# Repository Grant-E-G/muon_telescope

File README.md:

# Muon Telescope

This repository contains the complete design record for a two-layer cosmic-ray
muon telescope: electronics, FPGA firmware, host software, mechanical CAD,
manufacturing releases, and measurement records.

The first build is an engineering prototype. It uses two identical
50 x 50 x 10 mm BC-408 plastic-scintillator blocks and a central power/interface
board connected to a Digilent Cora Z7. The instrument is
intended to count single-channel events and two-layer coincidences. It is
**not** an energy spectrometer, position tracker, or scattering-tomography
system.

No PCB is approved for ordering yet. The current design and its remaining
release gates are recorded in [docs/design.md](docs/design.md) and
[docs/build-and-debug.md](docs/build-and-debug.md).

## Read first

1. [docs/design.md](docs/design.md) — authoritative electrical, FPGA, and
   measurement specification.
2. [docs/build-and-debug.md](docs/build-and-debug.md) — staged build, release
   gates, acceptance tests, and pre-populated debugging checklist.
3. [docs/bom.md](docs/bom.md) — sourced planning BOM and cost assumptions.
4. [docs/theory.md](docs/theory.md) — concise explanation of the signal chain
   and what the measurements can support.
5. [CONTRIBUTING.md](CONTRIBUTING.md) — KiCad and Git collaboration rules.

When documents disagree, `docs/design.md` wins unless a reviewed change updates
it. KiCad source becomes authoritative for connectivity only after the schematic
has been reviewed against that specification.

## Repository layout

```text
docs/                       Design, theory, BOM, build, debug, and datasheets
hardware/detector_head/     One KiCad design, assembled twice
hardware/power_interface/   Central power and Cora Z7 interface KiCad design
hardware/libraries/         Project symbols, footprints, and electrical 3D models
hardware/mechanical/        Frame, enclosure, and non-electrical CAD
hardware/manufacturing/     Reviewed, tagged fabrication packages only
firmware/                   Cora Z7 programmable-logic design and constraints
software/                   Host-side capture and analysis tools
data/                       Small, curated calibration and measurement records
scripts/                    Repeatable project checks
```

Keep source files near the subsystem they describe. Do not create another
directory or README unless it removes a real ambiguity. Large raw captures and
third-party source archives do not belong in Git; part datasheets are the
intentional exception and live in `docs/datasheets/`. For large raw captures,
record their external source and a checksum instead.

## Toolchain and routine checks

- KiCad **9.0.9** is the locked hardware file-format version.
- Run `make check` before a hardware pull request and before a fabrication
  release. The reusable checker reads each board's co-located `validation.json`
  and writes consolidated reports plus top/bottom review images under
  `build/checks/`. The run includes design-intent/layout checks and focused
  ngspice models; a clean DRC alone is not treated as validation.
- Preserve project-owned libraries and 3D models in this repository. Use
  project-relative `${KIPRJMOD}` library paths.

## Coding guidelines

- Prefer Rust for implementation work. Use Python as a backup, with type checking.
- Prefer functional code when possible. Relax this guideline when it causes performance issues.
- Long functions are fine.
- Avoid inheritance. Object-oriented design is generally discouraged.
- Avoid excessive code fragmentation. Longer files are acceptable when they keep related logic together.
- Lint code aggressively. Use Black for Python formatting.
- Shorter code is almost always better code.

## Attribution and license

The detector dimensions and front-end starting point were informed by the
[CosmicWatch Desktop Muon Detector v3X](https://github.com/spenceraxani/CosmicWatch-Desktop-Muon-Detector-v3X)
and its [2025 design paper](https://arxiv.org/html/2508.12111). No CosmicWatch
design files are copied here; consult its CC BY-NC 4.0 license before reusing
them. Original material in this repository is licensed under [MIT](LICENSE).

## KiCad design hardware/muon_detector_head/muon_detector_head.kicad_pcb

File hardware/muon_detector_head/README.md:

# Accepted prototype layout judgments: detector head and power/interface boards

The physical prototype release is **v0**, dated **2026-09-18**. Both sides of
both boards carry that identifier; the electrical design intent remains
revision A.

Both boards pass `make check` with no blocking findings. The layout still
contains three documented judgment calls. On 2026-09-17, the project owner
accepted all three as good enough for the revision-A engineering prototypes.
The acceptance freezes these layouts; it does not waive the remaining
physical-part, output-inspection, BOM, or release-package gates in
`docs/build-and-debug.md`.

Run `make check` (it needs KiCad 9.0.9 and `ngspice`) and review the reports
and renders under `build/checks/` alongside this list.

## 1. Relaxed ground-return distance for four bypass capacitors

**Where:** `proximity_checks` in `hardware/muon_detector_head/validation.json`
and `hardware/power_interface/validation.json`.

**What changed:** The checks required a bypass capacitor's ground pad to be
within 3.0 mm of the IC ground pin. On these packages, ground (pin 4) and
supply (pin 8) sit on opposite corners. A single component-side capacitor
therefore cannot be within 3.0 mm of both pins. The supply-side 3.0 mm limit
is unchanged; only the ground-side limit was raised.

| Board | Check | Old limit | New limit | Measured |
|---|---|---:|---:|---:|
| Head | U1 (TPH2502, SOIC-8) to C2 | 3.0 mm | 6.0 mm | 5.91 mm |
| Head | U3 (TPH2502, SOIC-8) to C17 | 3.0 mm | 6.0 mm | 5.91 mm |
| Head | U5 (SN74LVC1G123, DCT-8) to C15 | 3.0 mm | 4.5 mm | 3.92 mm |
| Power | U3 (MCP3202, SOIC-8) to C12 | 3.0 mm | 6.0 mm | 5.99 mm |

A brute-force search over capacitor position and rotation gives about 5.5 mm
as the best possible SOIC-8 result. On the real boards, neighbouring parts
push it to about 5.9 mm.

**Alternatives:** Put the capacitor on the back side (not allowed on the head:
the SiPM must be the only optical-side part). Or change the check to measure
each pad's distance to its own ground via instead of pad-to-pad.

**Resolution:** Accepted for the revision-A engineering prototypes. Retain the
configured limits and the measured-distance checks.

## 2. AMP_OUT passes between the R13 pads at 0.25 mm clearance

**Where:** rule `AMP_OUT between R_CHG pads` in
`hardware/muon_detector_head/muon_detector_head.kicad_dru`.

**Why:** The peak-hold checks place R13 within 3 mm of U3 pin 1, the BAS70
(D2) within 3 mm of C16, and C16 within 3 mm of U3 pin 5. C17 must sit at the
top end of U3. Together these leave the chain U3 pin 1 → R13 → D2 → C16 →
U3 pin 5 wrapped around the left side of U3, fencing in pin 3 (AMP_OUT). The
0.3 mm AMP_OUT trace enters pin 3 through the 0.8 mm gap between R13's pads.
That gives 0.25 mm clearance instead of the normal 0.4 mm. The U3A output, R13
and the diode anode follow AMP_OUT to within a diode drop, so the adjacent
signals are nearly identical. 0.25 mm is well within PCBWay's standard
capability.

**Alternatives:**
- A via pair on AMP_OUT. There is currently no room for the inner via.
- Route the chain around U3's other side. That needs the U3/C17 ground limit
  relaxed to about 7.5 mm.

**Resolution:** Accepted for the revision-A engineering prototypes. Retain the
0.25 mm local clearance rule and current route.

## 3. The PEAK_HOLD guard trace is now only a short piece

**Where:** head PCB around U3, C16, D2, Q1, U4 and TP11.

**Design intent:** `docs/design.md` asks for a narrow `PEAK_GUARD` trace that
surrounds the `PEAK_HOLD` island.

**What exists:** The hold node is now very compact. It runs under the U3 body
to C16, D2 pin 3, the Q1 drain, the U4 D pin (TMUX1101 alternate, DNP) and
TP11. Their neighbouring pads leave no legal room for a guard ring. There is
only:

- the U3 pin 6/7 link to R14, and
- a 3.5 mm guard piece beside Q1.

That piece's open end is the intentional `track_dangling` DRC warning.

**Trade-off:** The hold node is smaller, but less of it is guarded against
surface leakage.

**Alternatives:**
- Move the unfitted U4/C18 alternate out of the island to free space.
- Relax the peak-hold placement checks to make room for a full ring.

**Resolution:** Accepted for the revision-A engineering prototypes. Retain the
compact hold node and short guard piece, and qualify droop and leakage on the
bench as required by `docs/build-and-debug.md`.

## Other items for human review

These `make check` warnings were also accepted for the revision-A engineering
prototypes; they remain visible so bring-up and any future revision can address
measured problems rather than assuming the warnings are harmless:

- **Ground-plane coverage:** some routed nets have less than 95% ground plane
  underneath (listed per net in each report).
- **Bottom-layer routing:** some traces run on the B.Cu ground layer, cutting
  the plane.
- **Power board `TRIG_B`:** the trace is 6% over the one-sixth-edge
  transmission-line screen.
- **Head analytic noise floor:** the estimate is model-limited.

The layout for these changes was generated and edited with scripts, not in
the KiCad GUI. Open both boards in KiCad for the visual review that
`CONTRIBUTING.md` requires. The Gerbers under each `fab/` folder were
regenerated from the current boards. They are not a reviewed manufacturing
release.

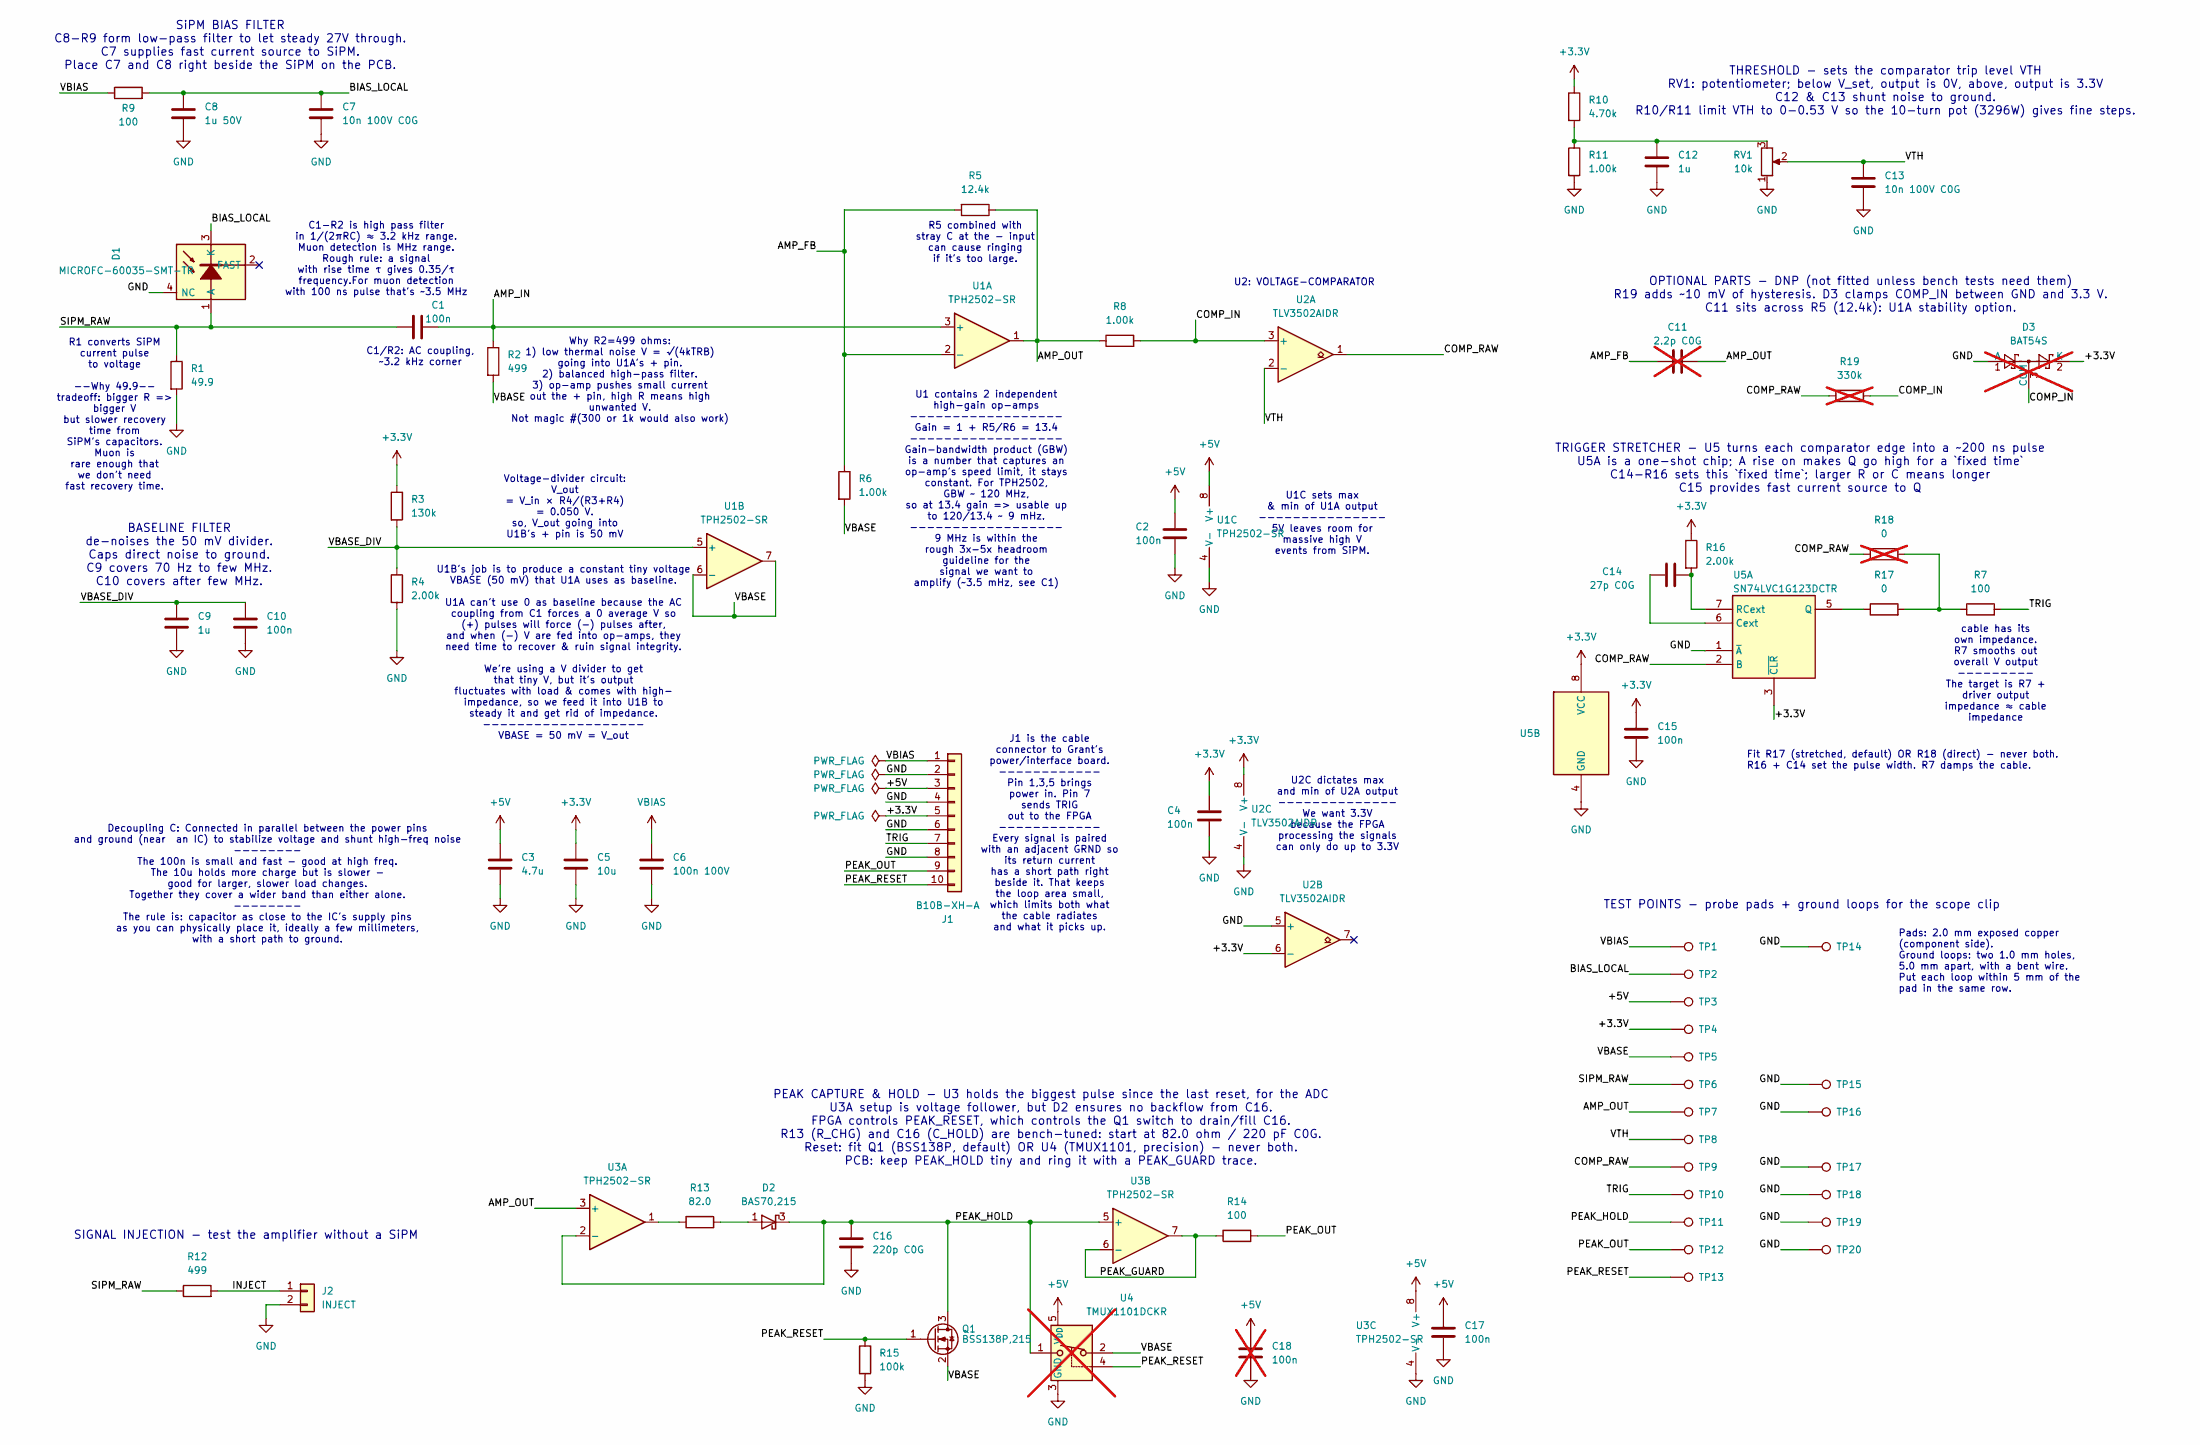
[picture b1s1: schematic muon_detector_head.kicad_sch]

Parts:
C1, C2, C4, C10, C15, C17: 100n; C_0805_2012Metric
C3: 4.7u; C_0805_2012Metric
C5: 10u; C_0805_2012Metric
C6: 100n 100V; C_0805_2012Metric
C7, C13: 10n 100V C0G; C_0805_2012Metric
C8: 1u 50V; C_1206_3216Metric
C9, C12: 1u; C_0805_2012Metric
C11: 2.2p C0G; C_0805_2012Metric; not fitted
C14: 27p C0G; C_0805_2012Metric
C16: 220p C0G; C_0805_2012Metric
C18: 100n; C_0805_2012Metric; not fitted
D1: MICROFC-60035-SMT-TR; MICROFC-60035-SMT
D2: BAS70,215; SOT-23
D3: BAT54S; SOT-23; not fitted
J1: B10B-XH-A; JST_XH_B10B-XH-A_1x10_P2.50mm_Vertical
J2: INJECT; PinHeader_1x02_P2.54mm_Vertical
Q1: BSS138P,215; SOT-23
R1: 49.9; R_0805_2012Metric
R2, R12: 499; R_0805_2012Metric
R3: 130k; R_0805_2012Metric
R4, R16: 2.00k; R_0805_2012Metric
R5: 12.4k; R_0805_2012Metric
R6, R8, R11: 1.00k; R_0805_2012Metric
R7, R9, R14: 100; R_0805_2012Metric
R10: 4.70k; R_0805_2012Metric
R13: 82.0; R_0805_2012Metric
R15: 100k; R_0805_2012Metric
R17: 0; R_0805_2012Metric
R18: 0; R_0805_2012Metric; not fitted
R19: 330k; R_0805_2012Metric; not fitted
RV1: 10k; Potentiometer_Bourns_3296W_Vertical
TP1: VBIAS; TestPoint_Pad_D2.0mm
TP2: BIAS_LOCAL; TestPoint_Pad_D2.0mm
TP3: +5V; TestPoint_Pad_D2.0mm
TP4: +3.3V; TestPoint_Pad_D2.0mm
TP5: VBASE; TestPoint_Pad_D2.0mm
TP6: SIPM_RAW; TestPoint_Pad_D2.0mm
TP7: AMP_OUT; TestPoint_Pad_D2.0mm
TP8: VTH; TestPoint_Pad_D2.0mm
TP9: COMP_RAW; TestPoint_Pad_D2.0mm
TP10: TRIG; TestPoint_Pad_D2.0mm
TP11: PEAK_HOLD; TestPoint_Pad_D2.0mm
TP12: PEAK_OUT; TestPoint_Pad_D2.0mm
TP13: PEAK_RESET; TestPoint_Pad_D2.0mm
TP14, TP15, TP16, TP17, TP18, TP19, TP20: GND_LOOP; TestPoint_GroundLoop_P5.00mm_Drill1.0mm
U1, U3: TPH2502-SR; SOIC-8_3.9x4.9mm_P1.27mm
U2: TLV3502AIDR; SOIC-8_3.9x4.9mm_P1.27mm
U4: TMUX1101DCKR; SOT-353_SC-70-5; not fitted
U5: SN74LVC1G123DCTR; SSOP-8_2.95x2.8mm_P0.65mm

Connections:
+3.3V: C4.1, C5.1, C15.1, D3.2 (K), J1.5 (+3V3_LOCAL), R3.1, R10.1, R16.1, TP4.1, U2.6 (-), U2.8 (V+), U5.3 (~CLR), U5.8 (VCC)
+5V: C2.1, C3.1, C17.1, C18.1, J1.3 (+5VA), TP3.1, U1.8 (V+), U3.8 (V+), U4.5 (V_{DD})
/AMP_FB: C11.1, R5.2, R6.1, U1.2 (-)
/AMP_IN: C1.2, R2.1, U1.3 (+)
/AMP_OUT: C11.2, R5.1, R8.1, TP7.1, U1.1, U3.3 (+)
/BIAS_LOCAL: C7.1, C8.1, D1.3 (K), R9.2, TP2.1
/COMP_IN: D3.3 (COM), R8.2, R19.2, U2.3 (+)
/COMP_RAW: R18.1, R19.1, TP9.1, U2.1, U5.2 (B)
/INJECT: J2.1, R12.2
/PEAK_GUARD: R14.1, U3.6 (-), U3.7
/PEAK_HOLD: C16.1, D2.3 (K), Q1.3 (D), TP11.1, U3.2 (-), U3.5 (+), U4.1
/PEAK_OUT: J1.9 (PEAK_OUT), R14.2, TP12.1
/PEAK_RESET: J1.10 (PEAK_RESET), Q1.1 (G), R15.1, TP13.1, U4.4
/SIPM_RAW: C1.1, D1.1 (A), R1.1, R12.1, TP6.1
/TRIG: J1.7 (TRIG_OUT), R7.2, TP10.1
/VBASE: Q1.2 (S), R2.2, R6.2, TP5.1, U1.6 (-), U1.7, U4.2
/VBASE_DIV: C9.1, C10.1, R3.2, R4.1, U1.5 (+)
/VTH: C13.1, RV1.2, TP8.1, U2.2 (-)
GND: C2.2, C3.2, C4.2, C5.2, C6.2, C7.2, C8.2, C9.2, C10.2, C12.2, C13.2, C15.2, C16.2, C17.2, C18.2, D1.4 (NC), D3.1 (A), J1.2 (GND), J1.4 (GND), J1.6 (GND), J1.8 (GND), J2.2, R1.2, R4.2, R11.2, R15.2, RV1.1, TP14.1, TP15.1, TP16.1, TP17.1, TP18.1, TP19.1, TP20.1, U1.4 (V-), U2.4 (V-), U2.5 (+), U3.4 (V-), U4.3 (GND), U5.1 (~A), U5.4 (GND)
unnamed: C12.1, R10.2, R11.1, RV1.3
unnamed: D2.1 (A), R13.2
unnamed: R13.1, U3.1
unnamed: R7.1, R17.2, R18.2
unnamed: C14.1, U5.6 (Cext)
unnamed: R17.1, U5.5 (Q)
unnamed: C14.2, R16.2, U5.7 (RCext)
VBIAS: C6.1, J1.1 (BIAS_27V), R9.1, TP1.1

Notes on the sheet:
R1 converts SiPM current pulse to voltage --Why 49.9-- tradeoff: bigger R => bigger V but slower recovery time from SiPM's capacitors. Muon is rare enough that we don't need fast recovery time.
BASELINE FILTER de-noises the 50 mV divider. Caps direct noise to ground. C9 covers 70 Hz to few MHz. C10 covers after few MHz.
SIGNAL INJECTION - test the amplifier without a SiPM
J1 is the cable connector to Grant's power/interface board. ------------ Pin 1,3,5 brings power in. Pin 7 sends TRIG out to the FPGA ------------ Every signal is paired with an adjacent GRND so its return current has a short path right beside it. That keeps the loop area small, which limits both wh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
cable has its own impedance. R7 smooths out overall V output --------- The target is R7 + driver output impedance ≈ cable impedance
Voltage-divider circuit: V_out = V_in × R4/(R3+R4) = 0.050 V. so, V_out going into U1B's + pin is 50 mV
SiPM BIAS FILTER C8-R9 form low-pass filter to let steady 27V through. C7 supplies fast current source to SiPM. Place C7 and C8 right beside the SiPM on the PCB.
OPTIONAL PARTS - DNP (not fitted unless bench tests need them) R19 adds ~10 mV of hysteresis. D3 clamps COMP_IN between GND and 3.3 V. C11 sits across R5 (12.4k): U1A stability option.
U2: VOLTAGE-COMPARATOR
R5 combined with stray C at the − input can cause ringing if it's too large.
Why R2=499 ohms: 1) low thermal noise V = √(4kTRB) going into U1A's + pin. 2) balanced high-pass filter. 3) op-amp pushes small current out the + pin, high R means high unwanted V. Not magic #(300 or 1k would also work)
U1C sets max & min of U1A output --------------- 5V leaves room for massive high V events from SiPM.
U1B's job is to produce a constant tiny voltage VBASE (50 mV) that U1A uses as baseline. U1A can't use 0 as baseline because the AC coupling from C1 forces a 0 average V so (+) pulses will force (-) pulses after, and when (-) V are fed into op-amps, they need time to recover & ruin signal integrity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
TRIGGER STRETCHER - U5 turns each comparator edge into a ~200 ns pulse U5A is a one-shot chip; A rise on makes Q go high for a `fixed time` C14-R16 sets this `fixed time`; larger R or C means longer C15 provides fast current source to Q
TEST POINTS - probe pads + ground loops for the scope clip
Fit R17 (stretched, default) OR R18 (direct) - never both. R16 + C14 set the pulse width. R7 damps the cable.
PEAK CAPTURE & HOLD - U3 holds the biggest pulse since the last reset, for the ADC U3A setup is voltage follower, but D2 ensures no backflow from C16. FPGA controls PEAK_RESET, which controls the Q1 switch to drain/fill C16. R13 (R_CHG) and C16 (C_HOLD) are bench-tuned: start at 82.0 ohm / 220 pF C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
Pads: 2.0 mm exposed copper (component side). Ground loops: two 1.0 mm holes, 5.0 mm apart, with a bent wire. Put each loop within 5 mm of the pad in the same row.
Decoupling C: Connected in parallel between the power pins and ground (near an IC) to stabilize voltage and shunt high-freq noise -------- The 100n is small and fast - good at high freq. The 10u holds more charge but is slower - good for larger, slower load changes. Together they cover a wider band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
C1-R2 is high pass filter in 1/(2πRC) ≈ 3.2 kHz range. Muon detection is MHz range. Rough rule: a signal with rise time τ gives 0.35/τ frequency.For muon detection with 100 ns pulse that's ~3.5 MHz
U1 contains 2 independent high-gain op-amps ------------------ Gain = 1 + R5/R6 = 13.4 ------------------ Gain-bandwidth product (GBW) is a number that captures an op-amp's speed limit, it stays constant. For TPH2502, GBW ~ 120 MHz, so at 13.4 gain => usable up to 120/13.4 ~ 9 mHz. ----------------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
C1/R2: AC coupling, ~3.2 kHz corner
U2C dictates max and min of U2A output -------------- We want 3.3V because the FPGA processing the signals can only do up to 3.3V
THRESHOLD - sets the comparator trip level VTH RV1: potentiometer; below V_set, output is 0V, above, output is 3.3V C12 & C13 shunt noise to ground. R10/R11 limit VTH to 0-0.53 V so the 10-turn pot (3296W) gives fine steps.

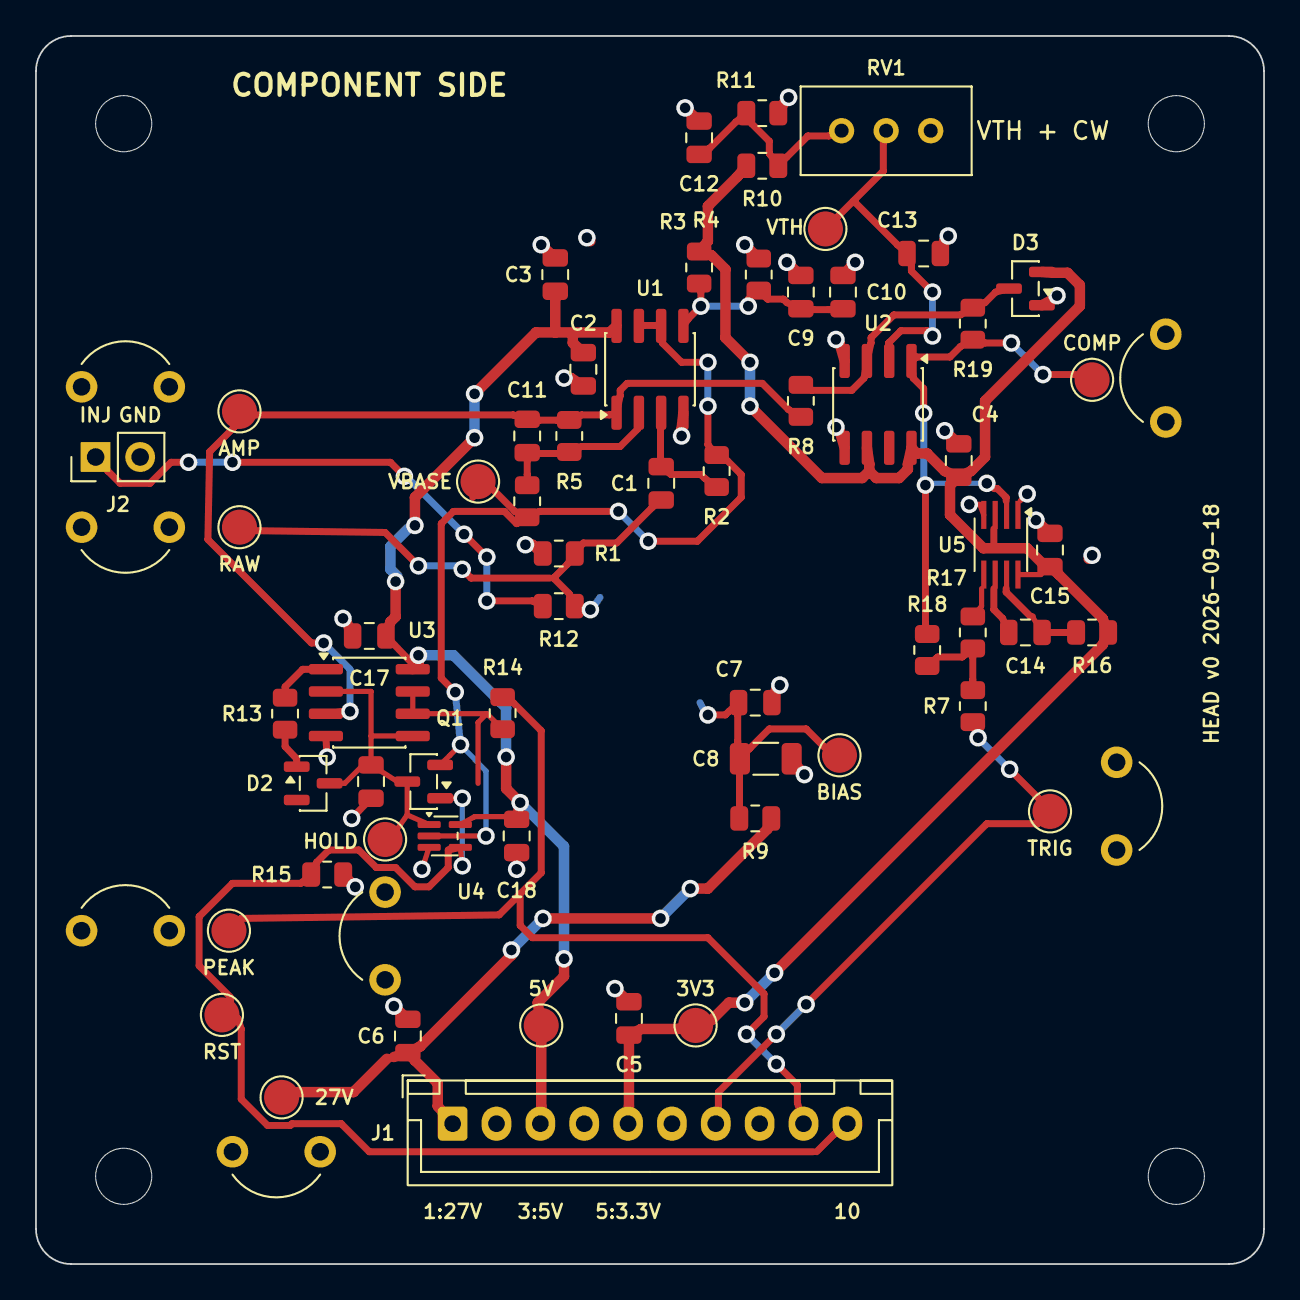
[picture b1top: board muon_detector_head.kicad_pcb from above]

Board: 2 copper layers, 70.0 x 70.0 mm, 73 parts (1 on the bottom side), 27 nets.

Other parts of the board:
H1, H2, H3, H4: MountingHole_3.2mm

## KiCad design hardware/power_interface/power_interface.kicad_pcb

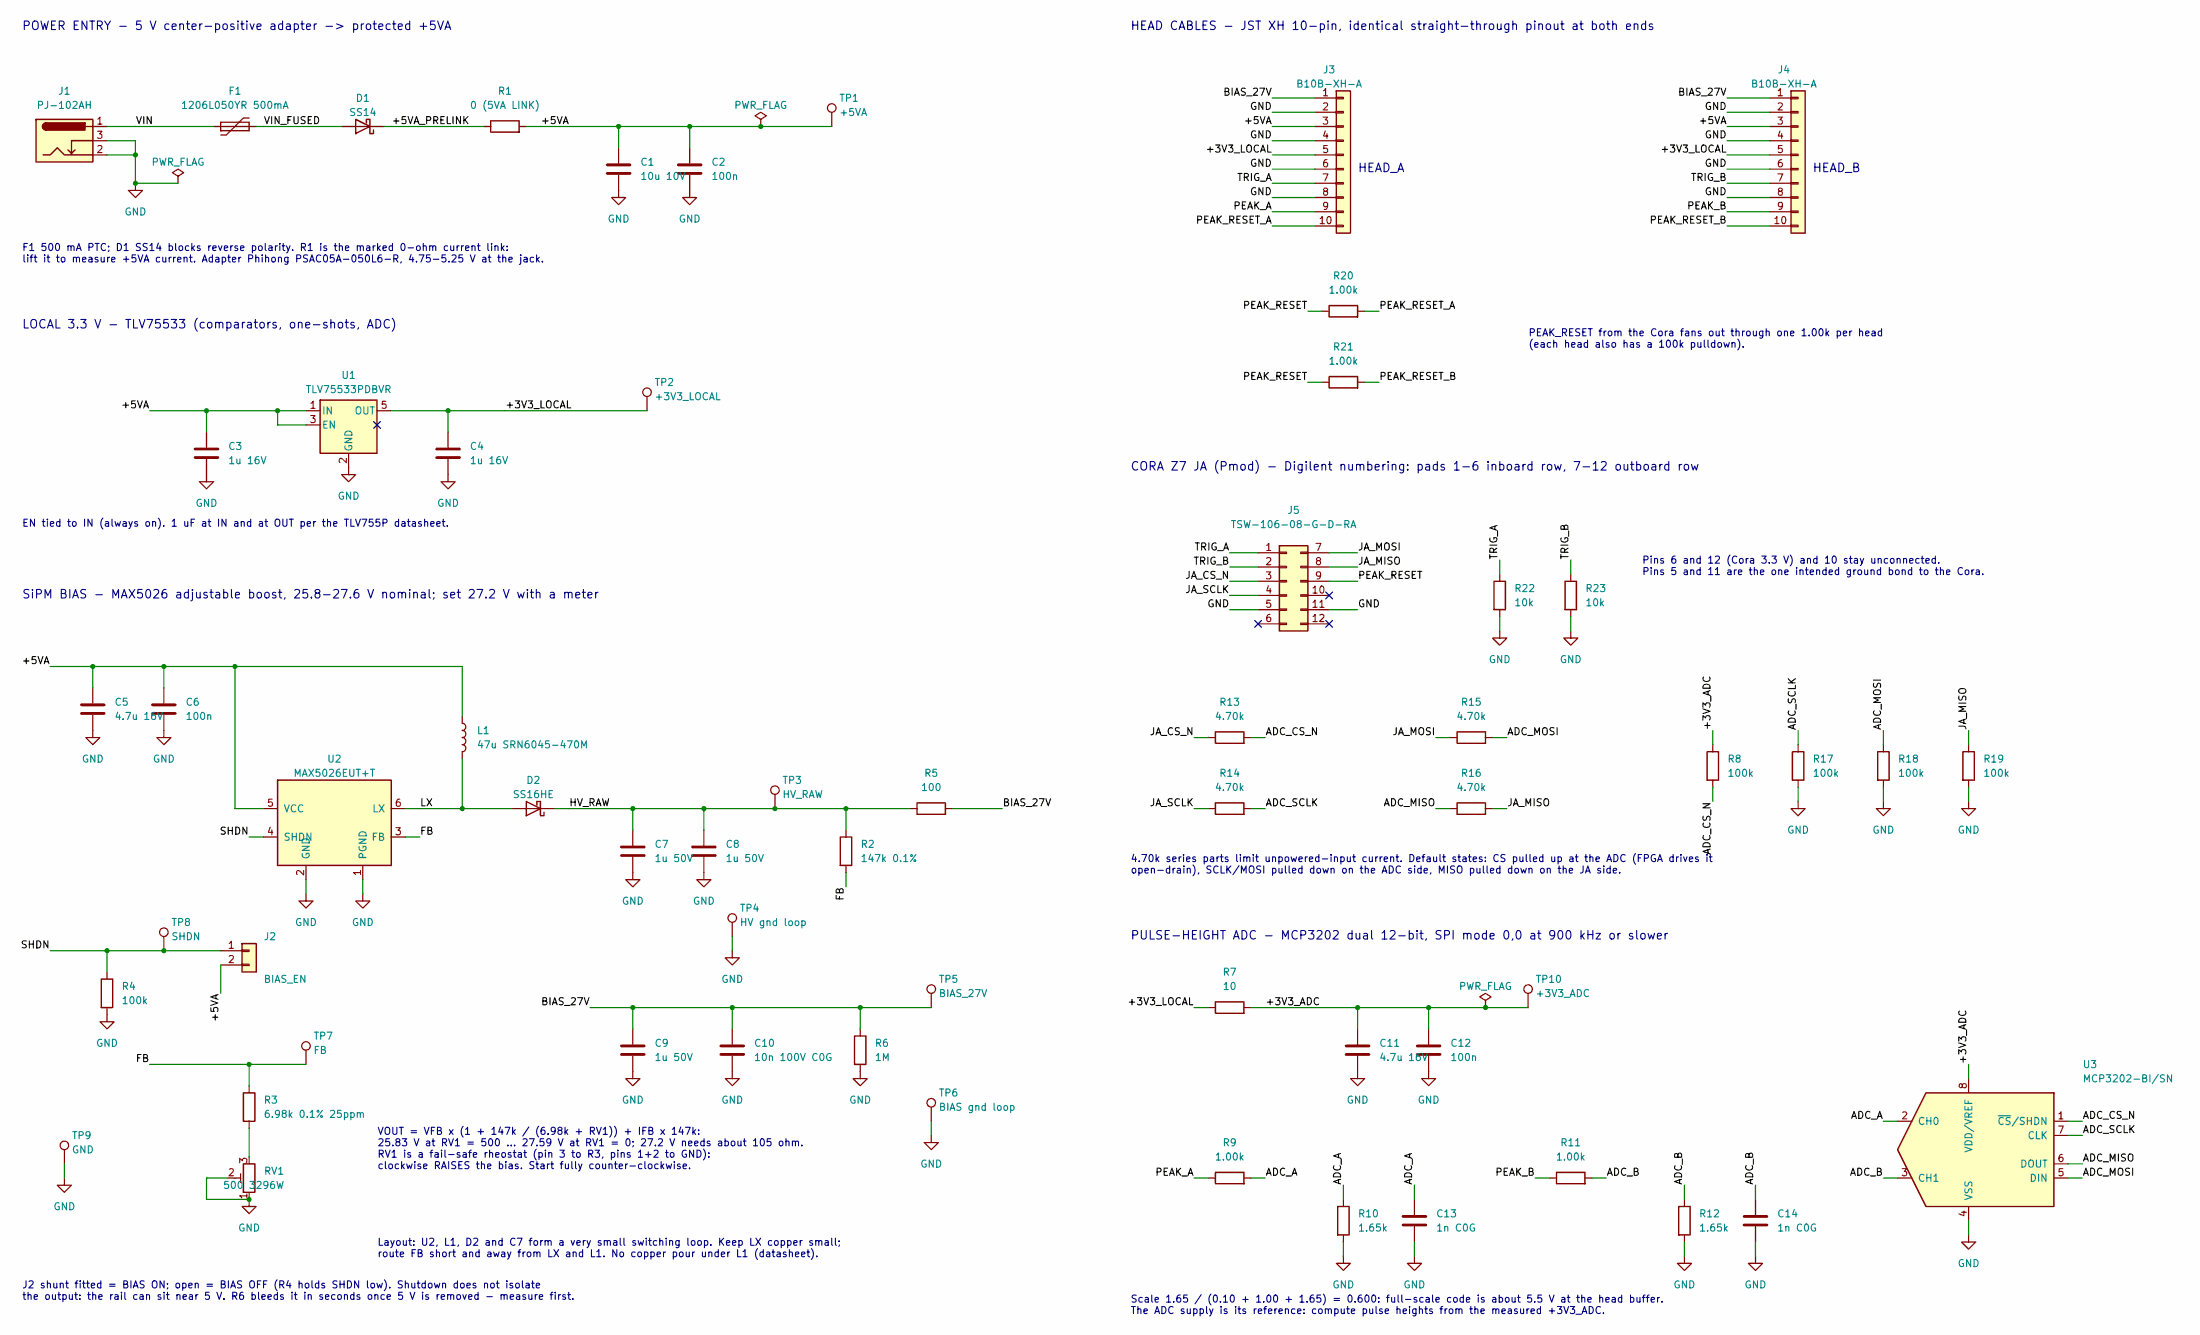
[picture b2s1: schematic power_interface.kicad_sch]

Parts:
C1: 10u 10V; C_1206_3216Metric
C2, C6, C12: 100n; C_0805_2012Metric
C3, C4: 1u 16V; C_0805_2012Metric
C5, C11: 4.7u 16V; C_0805_2012Metric
C7, C8, C9: 1u 50V; C_1206_3216Metric
C10: 10n 100V C0G; C_0805_2012Metric
C13, C14: 1n C0G; C_0805_2012Metric
D1: SS14; D_SMA
D2: SS16HE; D_SOD-323EP_onsemi_CASE-477AD
F1: 1206L050YR 500mA; Fuse_1206_3216Metric
J1: PJ-102AH; BarrelJack_CUI_PJ-102AH_Horizontal_EdgeMount
J2: BIAS_EN; PinHeader_1x02_P2.54mm_Vertical
J3, J4: B10B-XH-A; JST_XH_B10B-XH-A_1x10_P2.50mm_Vertical
J5: TSW-106-08-G-D-RA; PinHeader_2x06_P2.54mm_Horizontal_Pmod_TSW-106-08-G-D-RA
L1: 47u SRN6045-470M; L_Bourns_SRN6045
R1: 0 (5VA LINK); R_0805_2012Metric
R2: 147k 0.1%; R_0805_2012Metric
R3: 6.98k 0.1% 25ppm; R_0805_2012Metric
R4, R8, R17, R18, R19: 100k; R_0805_2012Metric
R5: 100; R_0805_2012Metric
R6: 1M; R_0805_2012Metric
R7: 10; R_0805_2012Metric
R9, R11, R20, R21: 1.00k; R_0805_2012Metric
R10, R12: 1.65k; R_0805_2012Metric
R13, R14, R15, R16: 4.70k; R_0805_2012Metric
R22, R23: 10k; R_0805_2012Metric
RV1: 500 3296W; Potentiometer_Bourns_3296W_Vertical
TP1: +5VA; TestPoint_Pad_D2.0mm
TP2: +3V3_LOCAL; TestPoint_Pad_D2.0mm
TP3: HV_RAW; TestPoint_Pad_D2.0mm
TP4: HV gnd loop; TestPoint_GroundLoop_P5.00mm_Drill1.0mm
TP5: BIAS_27V; TestPoint_Pad_D2.0mm
TP6: BIAS gnd loop; TestPoint_GroundLoop_P5.00mm_Drill1.0mm
TP7: FB; TestPoint_Pad_D2.0mm
TP8: SHDN; TestPoint_Pad_D2.0mm
TP9: GND; TestPoint_Pad_D2.0mm
TP10: +3V3_ADC; TestPoint_Pad_D2.0mm
U1: TLV75533PDBVR; SOT-23-5
U2: MAX5026EUT+T; SOT-23-6
U3: MCP3202-BI/SN; SOIC-8_3.9x4.9mm_P1.27mm

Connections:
/+3V3_ADC: C11.1, C12.1, R7.2, R8.1, TP10.1, U3.8 (VDD/VREF)
/+3V3_LOCAL: C4.1, J3.5, J4.5, R7.1, TP2.1, U1.5 (OUT)
/+5VA: C1.1, C2.1, C3.1, C5.1, C6.1, J2.2, J3.3, J4.3, L1.1, R1.2, TP1.1, U1.1 (IN), U1.3 (EN), U2.5 (VCC)
/+5VA_PRELINK: D1.1 (K), R1.1
/ADC_A: C13.1, R9.2, R10.1, U3.2 (CH0)
/ADC_B: C14.1, R11.2, R12.1, U3.3 (CH1)
/ADC_CS_N: R8.2, R13.2, U3.1 (~CS/SHDN)
/ADC_MISO: R16.1, U3.6 (DOUT)
/ADC_MOSI: R15.2, R18.1, U3.5 (DIN)
/ADC_SCLK: R14.2, R17.1, U3.7 (CLK)
/BIAS_27V: C9.1, C10.1, J3.1, J4.1, R5.2, R6.1, TP5.1
/FB: R2.2, R3.1, TP7.1, U2.3 (FB)
/HV_RAW: C7.1, C8.1, D2.1 (K), R2.1, R5.1, TP3.1
/JA_CS_N: J5.3, R13.1
/JA_MISO: J5.8, R16.2, R19.1
/JA_MOSI: J5.7, R15.1
/JA_SCLK: J5.4, R14.1
/LX: D2.2 (A), L1.2, U2.6 (LX)
/PEAK_A: J3.9, R9.1
/PEAK_B: J4.9, R11.1
/PEAK_RESET: J5.9, R20.1, R21.1
/PEAK_RESET_A: J3.10, R20.2
/PEAK_RESET_B: J4.10, R21.2
/SHDN: J2.1, R4.1, TP8.1, U2.4 (SHDN)
/TRIG_A: J3.7, J5.1, R22.1
/TRIG_B: J4.7, J5.2, R23.1
/VIN: F1.1, J1.1
/VIN_FUSED: D1.2 (A), F1.2
GND: C1.2, C2.2, C3.2, C4.2, C5.2, C6.2, C7.2, C8.2, C9.2, C10.2, C11.2, C12.2, C13.2, C14.2, J1.2, J1.3, J3.2, J3.4, J3.6, J3.8, J4.2, J4.4, J4.6, J4.8, J5.5, J5.11, R4.2, R6.2, R10.2, R12.2, R17.2, R18.2, R19.2, R22.2, R23.2, RV1.1, RV1.2, TP4.1, TP6.1, TP9.1, U1.2 (GND), U2.1 (PGND), U2.2 (GND), U3.4 (VSS)
unnamed: R3.2, RV1.3

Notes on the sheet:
POWER ENTRY - 5 V center-positive adapter -> protected +5VA
F1 500 mA PTC; D1 SS14 blocks reverse polarity. R1 is the marked 0-ohm current link: lift it to measure +5VA current. Adapter Phihong PSAC05A-050L6-R, 4.75-5.25 V at the jack.
LOCAL 3.3 V - TLV75533 (comparators, one-shots, ADC)
EN tied to IN (always on). 1 uF at IN and at OUT per the TLV755P datasheet.
SiPM BIAS - MAX5026 adjustable boost, 25.8-27.6 V nominal; set 27.2 V with a meter
VOUT = VFB x (1 + 147k / (6.98k + RV1)) + IFB x 147k: 25.83 V at RV1 = 500 ... 27.59 V at RV1 = 0; 27.2 V needs about 105 ohm. RV1 is a fail-safe rheostat (pin 3 to R3, pins 1+2 to GND): clockwise RAISES the bias. Start fully counter-clockwise.
J2 shunt fitted = BIAS ON; open = BIAS OFF (R4 holds SHDN low). Shutdown does not isolate the output: the rail can sit near 5 V. R6 bleeds it in seconds once 5 V is removed - measure first.
Layout: U2, L1, D2 and C7 form a very small switching loop. Keep LX copper small; route FB short and away from LX and L1. No copper pour under L1 (datasheet).
HEAD CABLES - JST XH 10-pin, identical straight-through pinout at both ends
HEAD_A
HEAD_B
PEAK_RESET from the Cora fans out through one 1.00k per head (each head also has a 100k pulldown).
CORA Z7 JA (Pmod) - Digilent numbering: pads 1-6 inboard row, 7-12 outboard row
Pins 6 and 12 (Cora 3.3 V) and 10 stay unconnected. Pins 5 and 11 are the one intended ground bond to the Cora.
4.70k series parts limit unpowered-input current. Default states: CS pulled up at the ADC (FPGA drives it open-drain), SCLK/MOSI pulled down on the ADC side, MISO pulled down on the JA side.
PULSE-HEIGHT ADC - MCP3202 dual 12-bit, SPI mode 0,0 at 900 kHz or slower
Scale 1.65 / (0.10 + 1.00 + 1.65) = 0.600: full-scale code is about 5.5 V at the head buffer. The ADC supply is its reference: compute pulse heights from the measured +3V3_ADC.

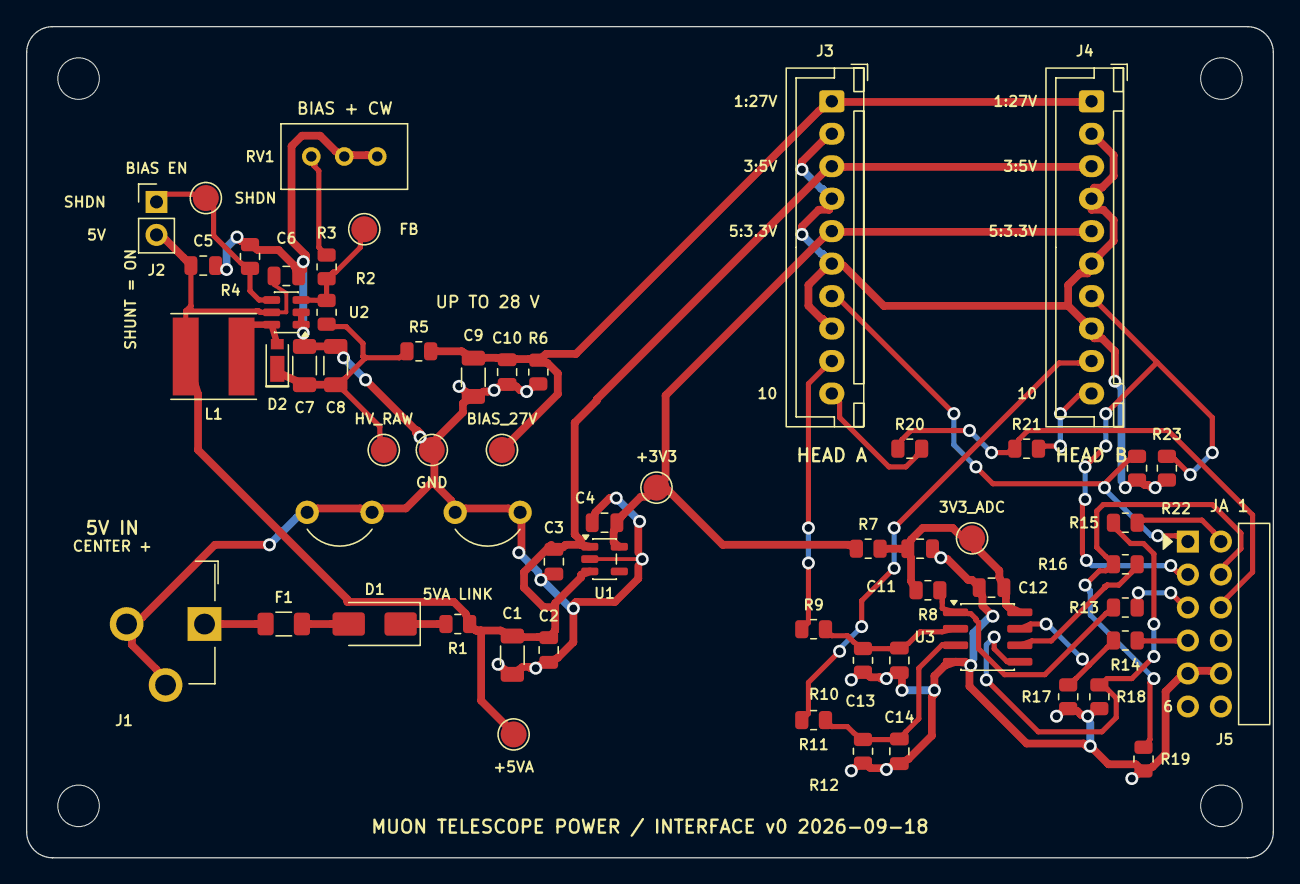
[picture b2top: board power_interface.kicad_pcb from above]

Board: 2 copper layers, 96.0 x 64.0 mm, 64 parts (0 on the bottom side), 30 nets.

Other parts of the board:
H1, H2, H3, H4: MountingHole_3.2mm
